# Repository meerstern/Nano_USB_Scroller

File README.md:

# Nano USB Volume

# Overview
  * This board is equipped with scroll and center button functions.  
  * It supports volume control and mute with center button operation.  
  * Suitable for small PCs and SBCs(Single Board Computers, like Raspberry Pi).  
  * It operates using standard drivers, without the need for a dedicated driver.   
  * The vertical scrolling direction can be changed to match the USB orientation.  

# Direction Setting
  * To change the volume direction, press and hold the center button while connecting the device to the USB port.  
  * The settings will be applied immediately.
  * If the settings are not applied, please perform the procedure again.  
  * The configuration data is automatically saved to flash memory.   
  * The orientation does not need to be set again for subsequent uses.  
  * The configuration data supports up to approximately 10,000 rewrite cycles.  
  * If you do not wish to change the orientation, connect this device to the USB port without pressing the center button.
  * To reverse the direction, perform the operation again to return it to the original state.

# Note
  * Please take care not to short-circuit or damage components on the back of the board.    
  * Please operate gently. Operating it with excessive force may cause damage.  
  * PCB color, LED color, and other specifications are subject to change without notice.

## Appearance and examples

Combination use with the USB Nano Mouse

[1]: https://github.com/meerstern/Nano_USB_Mouse/

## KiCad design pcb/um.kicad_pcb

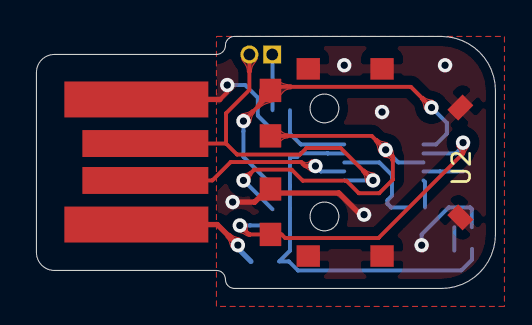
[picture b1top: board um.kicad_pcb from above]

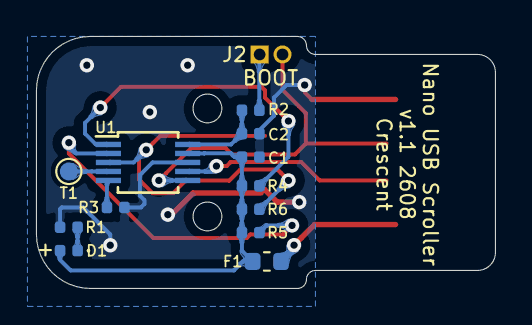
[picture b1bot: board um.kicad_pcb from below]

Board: 2 copper layers, 25.5 x 14.0 mm, 15 parts (12 on the bottom side), 13 nets.

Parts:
C1, C2: 0.1u; C_0402_1005Metric
D1: GREEN; LED_0402_1005Metric
F1: 300mA; Fuse_0603_1608Metric
J1: USB_A; usbpcb
J2: BOOT; PinHeader_2x01_P1.27mm_Vertical
R1, R2, R3: 2.2k; R_0402_1005Metric
R4, R5, R6: 10k; R_0402_1005Metric
T1: TEST; TestPoint_Pad_D1.0mm
U1: CH554E; MSOP-10_3x3mm_P0.5mm
U2: SIQ-02FVS3

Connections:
+3V3: C2.1, R2.1, U1.10
+5V: C1.1, D1.2, F1.2, R4.1, R5.1, R6.1, U1.9
/DM: J1.2, U1.7
/DP: J1.3, J2.2, U1.6
/ENC_A: R4.2, U1.1, U2.A
/ENC_B: R5.2, U1.2, U2.B
/RST: R3.1, U1.5
/SLIDE_SW: R6.2, U1.3, U2.S
GND: C1.2, C2.2, J1.4, R1.2, R3.2, U1.8, U2.C, U2.F
unnamed: D1.1, R1.1
unnamed: F1.1, J1.1
unnamed: J2.1, R2.2
unnamed: T1.1, U1.4
